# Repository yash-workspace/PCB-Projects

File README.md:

# My PCB Design Journey

Welcome! This repository is a living document of my hands-on journey into the world of PCB design and practical electronics using KiCad.

For me, this isn't just about connecting dots on a screen or getting an LED to blink. It’s about deeply understanding what happens beneath the surface—mastering current flow, grounding, return paths, routing strategies, and designing for actual manufacturability.

Instead of blindly copying tutorial schematics, I build these projects from the ground up using **datasheets, engineering research, messy experimentation, and iterative redesigns** based on real-world feedback.

---

# The Toolkit

* **Design:** KiCad 10
* **Version Control:** Git & GitHub (because breaking things is part of the process)
* **Validation:** Rigorous DRC/ERC workflows
* **Knowledge Base:** Deep-dives into datasheets & community code reviews

---

# Repository Structure

```text
PCB-Projects/
│
├── Project_01_LED_Driver/   # My gateway project (Transistor-based)
│
├── Project_02_...          # Incoming designs...
│
└── Future Projects/         # The roadmap

```

---

# The Projects

## Project 01 — LED Driver PCB (V2)

My gateway into hardware: a transistor-based LED driver utilizing a PN2222A transistor, a current-limiting resistor, a push-button switch, and a 12V input.

While the circuit itself is fundamental, the real challenge was transitioning from a breadboard mindset to a hardware manufacturing mindset. I used this project to cut my teeth on schematic capture, copper pours, proper grounding, and wrestling with DRC/ERC errors.

### The Evolution: V1 → V2

Design is iterative, and V1 had plenty of room for improvement. Here is what changed in the second revision:

* **Better Power Delivery:** Added a dedicated GND copper pour and optimized current return paths.
* **Cleaner Routing:** Overhauled the trace strategy for cleaner signal flow and better organization.
* **Mechanical Basics:** Added mounting holes and clear, legible silkscreen labels for easier debugging.
* **Production Ready:** Fixed lingering DRC/ERC issues to ensure the board can actually be fabricated.

 **Explore the project files:** Check out the `Project_01_LED_Driver/` folder.

---

# What I’m Chasing Next

### Current Focus

* Solidifying PCB layout fundamentals
* Mastering datasheet-driven design
* Developing a reliable hardware debugging workflow
* Bridging the gap between embedded systems and physical hardware

### On the Horizon

* Moving to MOSFET switching and complex power electronics
* Stepping up to dense 2-layer (and eventually multi-layer) designs
* Designing custom microcontroller (MCU) boards and sensor interfaces
* Robotics electronics

---

# A Key Lesson So Far

If there is one major takeaway I've had so far, it’s this:

> **Schematics define electrical intent. PCB layout defines physical electromagnetic implementation.**

Even the simplest 12V circuit forces you to balance electrical engineering, mechanical constraints, and the physics of how current actually behaves on copper.

---

# Project Status

**Actively building, breaking, and iterating.** Feel free to look around, check out the schematics, or drop some feedback if you see room for improvement!

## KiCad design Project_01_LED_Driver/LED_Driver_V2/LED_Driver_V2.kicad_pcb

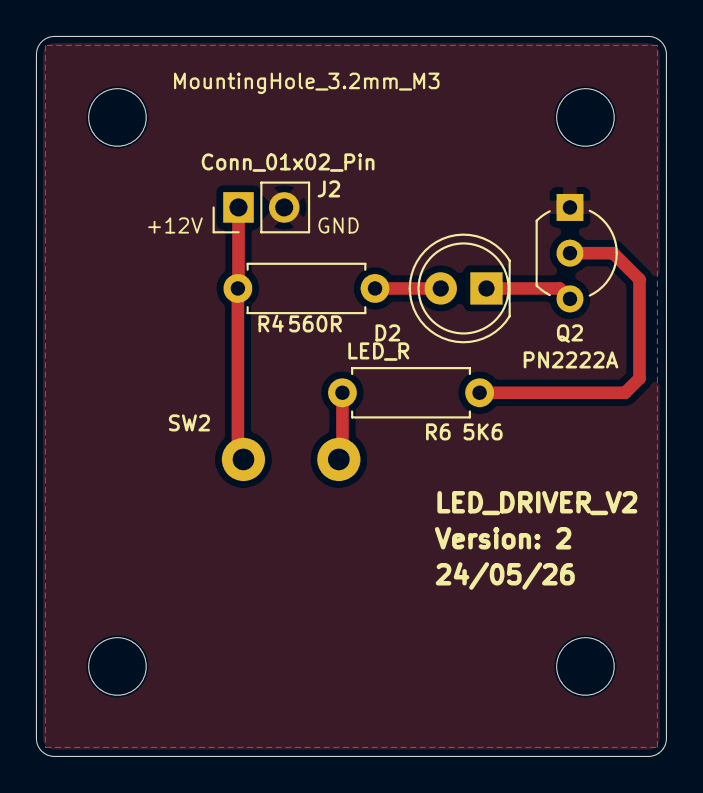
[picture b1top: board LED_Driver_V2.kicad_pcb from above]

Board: 2 copper layers, 35.0 x 40.0 mm, 6 parts (1 on the bottom side), 6 nets.

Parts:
D2: LED_R; LED_D5.0mm
J2: Conn_01x02_Pin; PinHeader_1x02_P2.54mm_Vertical
Q2: PN2222A; TO-92_Inline_Wide
R4: 560R; R_Axial_DIN0207_L6.3mm_D2.5mm_P7.62mm_Horizontal
R6: 5K6; R_Axial_DIN0207_L6.3mm_D2.5mm_P7.62mm_Horizontal
SW2: SW_CW_GPTS203211B

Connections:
+12V: J2.1, R4.1, SW2.1 (A)
GND: J2.2, Q2.1 (E)
unnamed: D2.2 (A), R4.2
unnamed: D2.1 (K), Q2.3 (C)
unnamed: Q2.2 (B), R6.1
unnamed: R6.2, SW2.2 (B)

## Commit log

2026-05-25 Added Project 01 LED Driver PCB
2026-05-25 Cleaned and organized Project 01 repository structure
2026-05-25 Create README.md for PCB design journey
    Added a comprehensive README detailing my PCB design journey, toolkit, project structure, and lessons learned.
2026-05-25 Simplify README introduction
    Removed introductory text to streamline README.
